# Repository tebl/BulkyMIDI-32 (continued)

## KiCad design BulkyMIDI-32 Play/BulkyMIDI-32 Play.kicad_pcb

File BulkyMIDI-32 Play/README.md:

# BulkyMIDI-32 Play
In many ways the missing module when it comes to playing around with a Roland MT-32, both the vintage kind as well as the emulated version that is the main BulkyMIDI-32 module (running mt32-pi) - simply playing back a .MID-file without a computer attached to it. Implemented with an Arduino Pro Micro at its heart, you can put your files on an SD-card and play them back - use a long press when starting playback to loop the file, another long press to stop playback. During playback the rotary encoder encoder can be used to speed up or slow down the tempo.

Given that the design includes provisions for more than the expected number of MIDI-ports, a change in firmware can allow the hardware design to be used for entirely different purposes such as MIDI-message filtering, merging inputs and similar functionality.

- [1> Building the device](#1-building-the-device)
  - [1.1> Soldering it together](#11-soldering-it-together)
  - [1.2> Without front panel](#12-without-front-panel)
  - [1.3> Including front panel](#13-including-front-panel)
  - [1.4> Finishing touches](#14-finishing-touches)
- [2> Schematic](#2-schematic)
- [3> BOM](#3-bom)

# 1> Building the device
Building a device such as this assumes you have at least minor experience soldering things together, recommended is that you at the very least have access to a soldering station with adjustable temperature. If currently available, you should probably start with 60/40 rosin core solder as the lead-free alternatives tends to be a bit harder to work with.

With requirements for basic equipment sorted, we need to talk a bit about what you want to achieve while building this project. The reason I ask is that while you can build a functional *BulkyMIDI-32 Audio Switch* by using this module by itself, but there is certainly the option of building the complete version of it - including front panels, faceplates for the top of the unit and so on. 

Now that you know what you want to build, we can get started on the most expensive step in any build process - shopping! So, head on over to the [BOM](#3-bom)-section for some information on what kind of components that you'll need. While I would have liked to give you specific part numbers for "reputable" electronic part suppliers, I can't afford to shop there so I usually make due with what I can find on sites such as ebay, AliExpress and any similar sites that sell cheap chinese components. The downside to this is that I can't link to a part directly and expect it to stay listed, so you'll need to consider the description listed as suggested search terms.

## 1.1> Soldering it together
The construction of this unit should be fairly straight-forward, just take your time in order to make sure everything goes into place - more or less straight. I usually recommend starting by having a good look at the PCBs, try to figure out where all of the listed components go and in which orientation they go in (most of the information should be clearly marked on the silkscreen).

I will usually try to install components sorted by their physical size, doing it this way means you'll have an easier time keeping everything from looking somewhat crooked. This is your board, your build and you want it perfect - don't you? If you said no, then go sit in the corner because I worked hard on creating this for myself and whoever wants to build one.

Here we've already gotten started by installing all of the resistors needed, making sure that we use the correct values for each position on the board. While doing this, it is always a good recommendation to try and keep the colour bands in the same orientation - mostly because it makes it easier to spot mistakes later on.

There are spots for a couple of 1n4148 diodes in several locations on the board, while these will not be used by the standard firmware for the *BulkyMIDI-32 Play*-module. Mostly in case I want to use the board for something else at a later point in time. The diodes are polarized, for that reason we need to pay particular attention so that the black band matches up with that of the markings on the PCB.

Sockets should be installed for the ICs, I've even added those that can be considered optional. With that in place I've also installed the monolithic disc capacitors, these are all unpolarized and for the ones without any specific markings we will install 100nF capacitors (the code *104* will be printed on them).

I added the pin headers for the *Arduino Pro Micro*, these come in variations that have slightly varying widths so one side will have two sets of pins. The Arduino itself will have female pin headers soldered to it, so this won't be an issue later - the reason for doing this way is that I might want to recycle the Arduino for a later project and this change makes it a lot easier to do so.

I'm using a fairly common *MicroSD Card Adapter* for my projects, usually you can find these in packs of three or more so they are easy to use as long as you have the board space for them (that way I don't have to think about voltage regulation when dealing with the SD-cards directly). The installation is easy, just add some thick doublesided tape to the top of the slot and insert the adapter upside down into the holes for it. It's probably not recommended to do so, but I usually just use the PCB itself to bend the right-angle pin headers until it goies into position.

Finally I added the single polarized capacitors, these need to go in the right way for them to function as expected. The stripe on the side of the capacitor denotes the negative side of it, this should be matched up with the filled in area of the footprint. I've also added a DC barrel connector (5.5mm x 2.1mm) to the board.

Add 20mm hex standoffs to each corner of the board, fixing them with nuts on the underside. Depending on your life decisions up to this point, the assembly from this point continues in one or the other direction:
- [1.2> Without front panel](#12-without-front-panel)
- [1.3> Including front panel](#13-including-front-panel)

## 1.2> Without front panel
So you resisted the temptation to build the complete version, choosing instead to cut corners where possible? Well, good for you. I'm not judging - it was just a general observation.

There's much that we need to do, mainly just install the two 5mm LEDs on the board - the longer LED pin goes into the round pad. The four switches are standard right-angle switches, the recommended way to install them is simply to solder a single pin then reheat and adjust its alignment before soldering in the rest of the pins.

- [1.4> Finishing touches](#14-finishing-touches)

## 1.3> Including front panel

The [Play Panel](https://github.com/tebl/BulkyMIDI-32/tree/main/BulkyMIDI-32%20Play%20Panel) have its own set of documentation going into the various steps required to put it together correctly, a finished unit have already been installed on the device as shown already. The clue to get it right is ensuring that one of the *flat* sides of the 20mm standoffs point towards the inside of the PCB. With the alignment correct you should be able to insert the panel into the board without too much force, if you have one I recommend that you try installing your selected faceplate on top of the device using screws.

At this point we've not actually soldered the various boards together, mostly to ensure that everything comes together correctly before we actually do so. Push the panel firmly so that it sits towards the back of the cutouts, before finally soldering the pins into place - afterwards we just make sure to trim the excess parts of the pin headers from the underside of the device to prevent any accidental shorting.

- [1.4> Finishing touches](#14-finishing-touches)

## 1.4> Finishing touches

If you've made it this far, you're almost ready to simply start using it. What's missing in order to test it is the single IC that needs to be inserted into the socket, so just get that out of the way before you forget to do so. The device is powered using a 5v DC barrel jack (center positive). These should be easy to obtain from your favourite electronics vendor, just make sure that it's from a somewhat respected brand.

The only step that's remaining to do when it comes to the hardware is just to screw the faceplates back on the top of the device, once that's in place we can also add the front panel as well.

The [firmware](https://github.com/tebl/BulkyMIDI-32/tree/main/software/arduino/Play) that was developed for the device have been included in the software-portion of this repository. The code itself was written using PlatformIO environment though it should be compilable using the standard *Arduino IDE*, if you should prefer to do so. 

# 2> Schematic
The supplied KiCad files should be sufficient as both a schematic and as a  starting point for ordering PCBs (basically you could just zip the contents of the export folder and upload that on a fabrication site), the schematic is also available in [PDF-format](https://github.com/tebl/BulkyMIDI-32/tree/main/documentation/schematic) and this is what you'll need to print and work your way through this things don't work as expected after assembly.

# 3> BOM
Most parts should be easy to get a hold of from your favourite local electronic component shop, but given that I don't have access to such shops where I live so everything was based on whatever I could get cheapest from eBay/AliExpress (free shipping, but plan on waiting 3-4 weeks for delivery). Components in parenthesis can be considered optional for features beyond the more basic functionality, but where's the fun in that? You deserve the complete package.

| Reference             | Item                                                              | Count | Order  |
| --------------------- | ----------------------------------------------------------------- | ----- | ------ |
| PCB                   | Fabricate using Gerber files                                      |     1 | PCBWay
| [Panel PCB](https://github.com/tebl/BulkyMIDI-32/tree/main/BulkyMIDI-32%20Play%20Panel) | Fabricate using Gerber files                                      |    (1)| PCBWay
| A1                    | Arduino Pro Micro                                                 |     1 |
|                       |  - Breakable straight pin headers                                 |     1 |
|                       |  - 12-pin female pin header                                       |     2 |
| A2                    | MicroSD Card Adapter module                                       |     1 |
| C1                    | 100nF ceramic capacitor (5mm)                                     |     1 |
| C2,C7                 | 100nF ceramic capacitor (5mm)                                     |    (2)|
| C6                    | 470uF electrolytic capacitor (8mm x 3.5mm)                        |     1 |
| D1,D2 *               | 5mm LED                                                           |    (2)|
| D3,D4                 | 1N4148N small signal diode (DO-35)                                |    (2)|
| IC1 *                 | 0.91 inch oled display                                            |    (1)|
| J1                    | 2.1mm x 5.5mm barrel plug                                         |     1 |
| JP1                   | Breakable straight pin header and jumper cap                      |     1 |
| R1-R3,R6,R8-R10,R18   | 220 ohm resistor                                                  |     8 |
| R4,R5                 | 330 ohm resistor                                                  |     2 |
| R7,R19                | 2kk (2200) ohm resistor                                           |     2 |
| SW1-SW6 *             | 6x6x5mm right-angle momentary button                              |    (4)|
| U1                    | 74HCT14 (DIP-14)                                                  |     1 |
| Mounting ****         | Nylon M3 hex standoffs 20mm (M-F)                                 |     4 |
| Mounting ****         | Nylon M3x6mm nylon screws                                         |     4 |
| Mounting ****         | Nylon M3x6mm nylon nuts                                           |     4 |

*) You can choose to install a front panel, in which case you would skip the installation of the 3mm LED as well as the switches. The resistors will be used by the front panel.

****) These are available in the form of kits usually advertised *M3 nylon standoff kit* which should contain most of what you'd need. I do however recommend that you pick up extra M-F standoffs of lengths 8mm and 20mm, as quite a lot of them will be used when building more than one module.

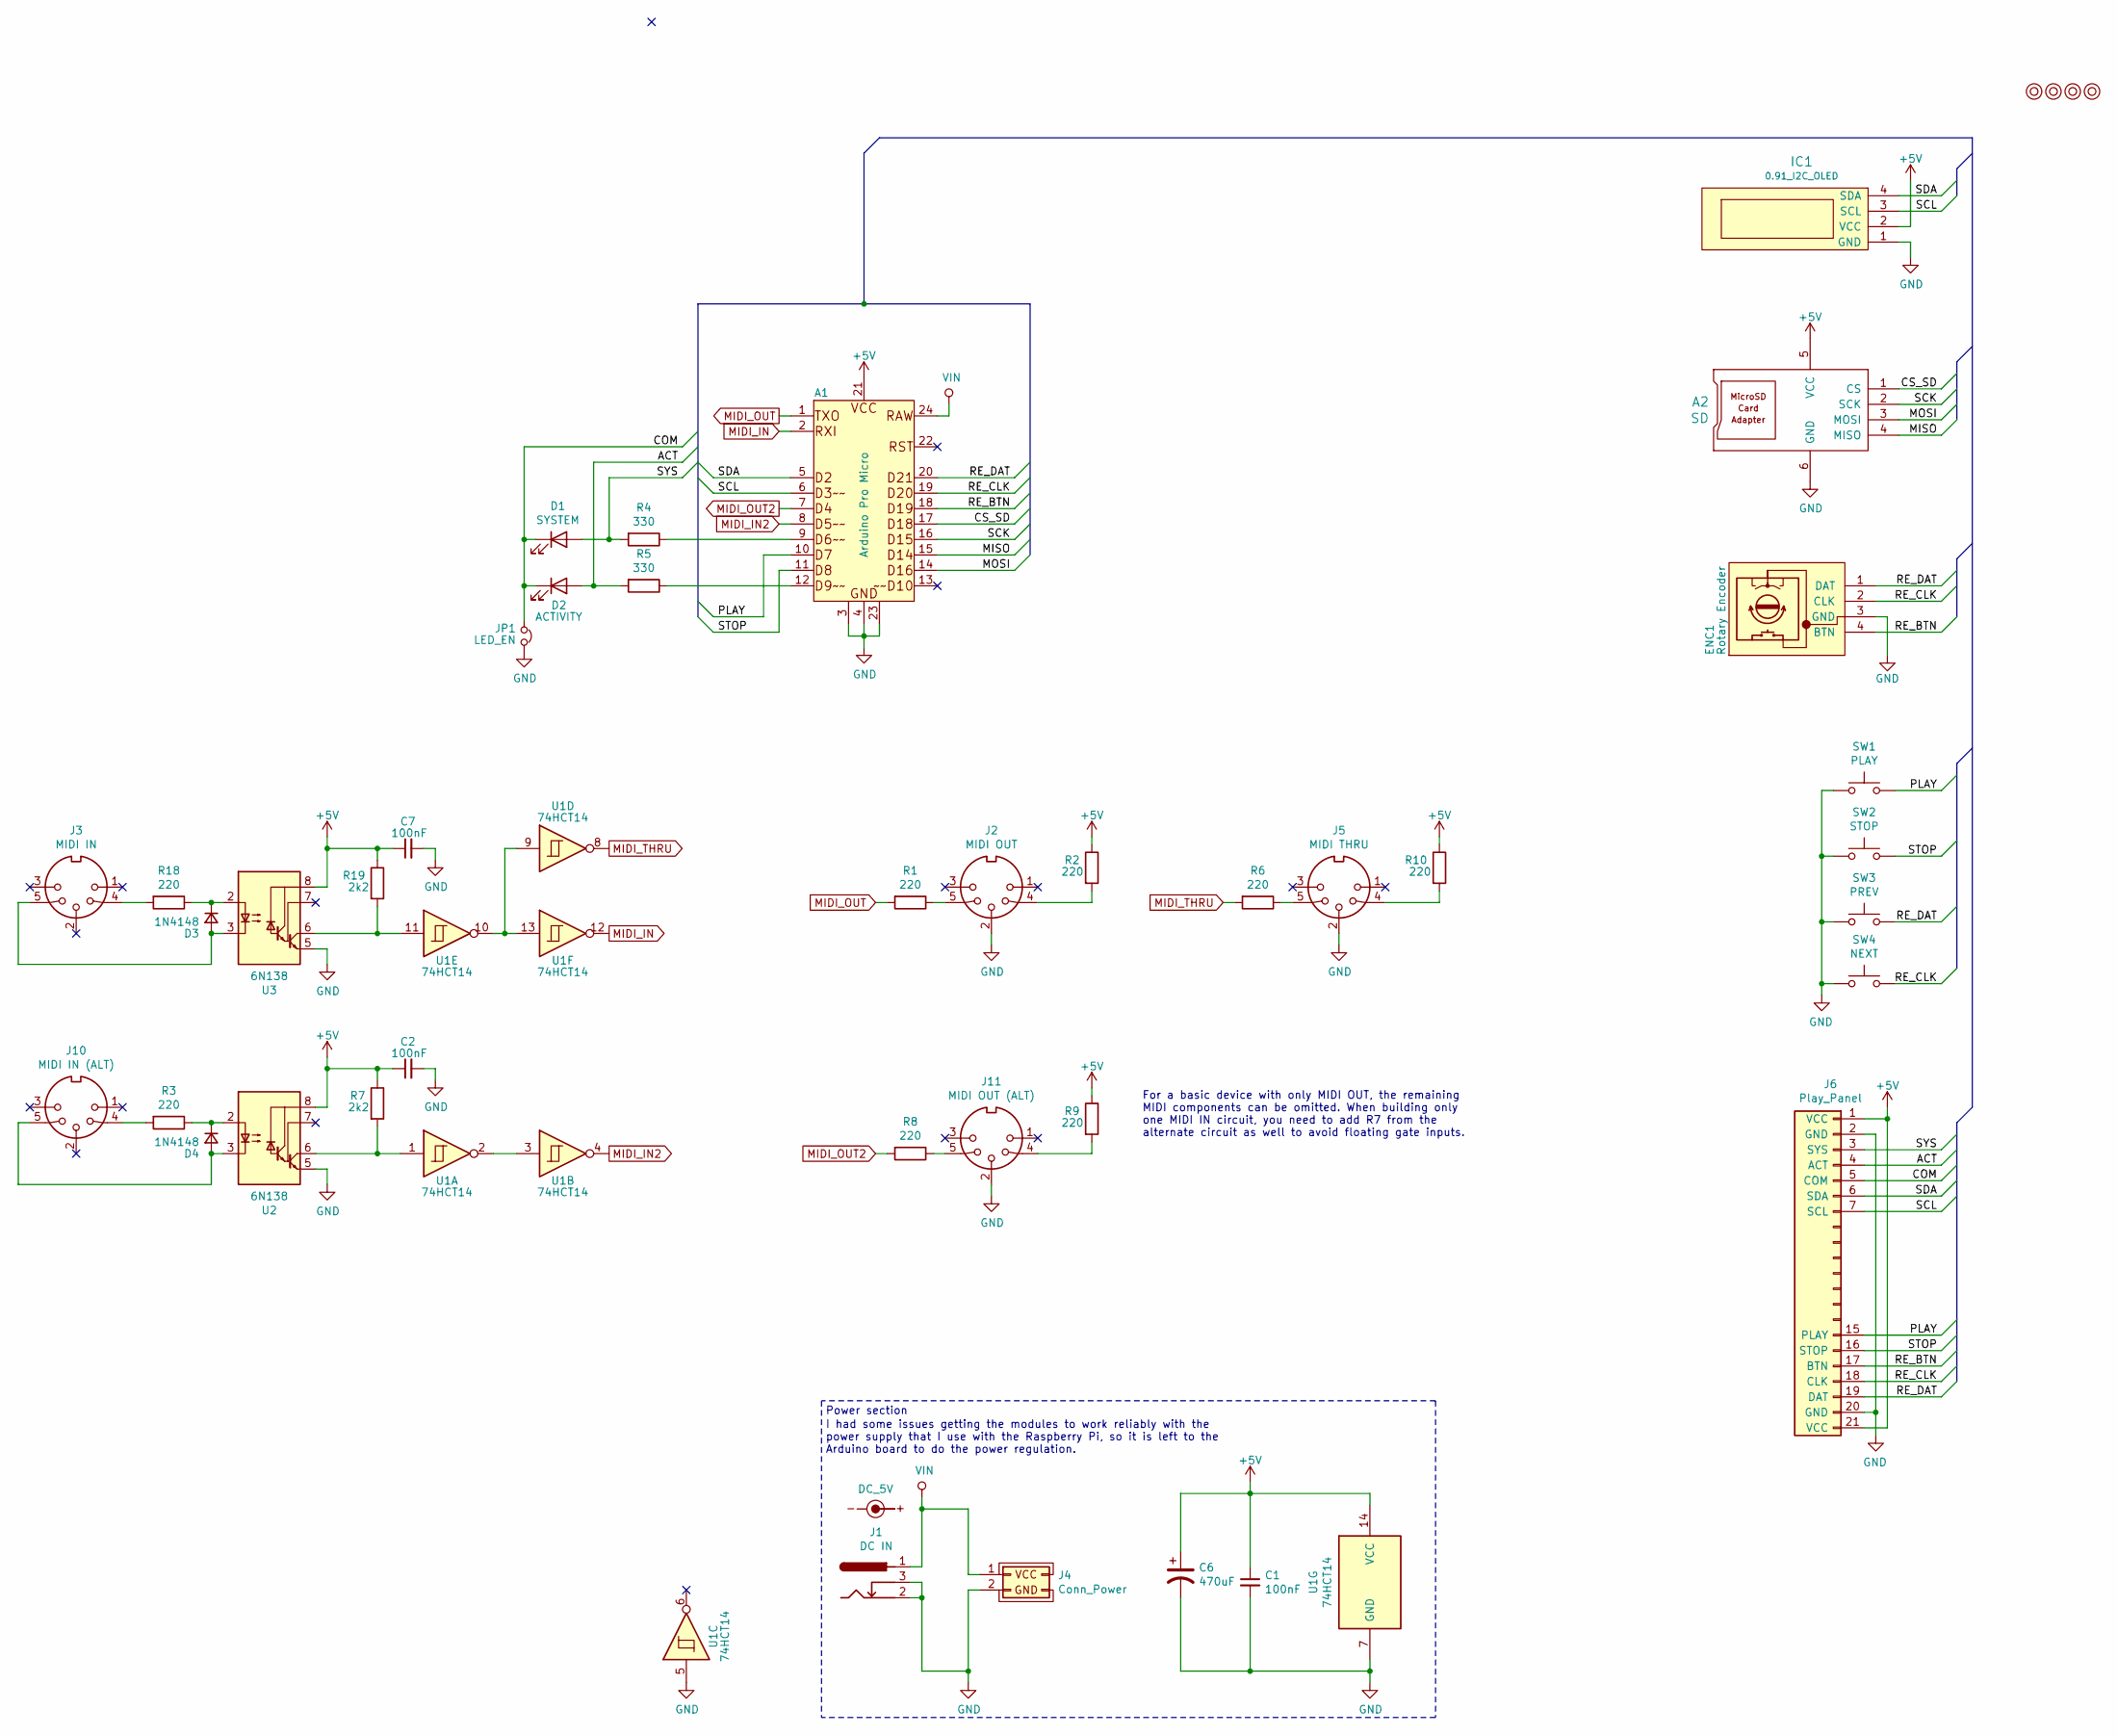
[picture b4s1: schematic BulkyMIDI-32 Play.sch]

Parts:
A1: Arduino Pro Micro; Arduino_Pro_Micro
A2: SD; MicroSD_Card_Adapter
C1, C2, C7: 100nF; C_Disc_D4.7mm_W2.5mm_P5.00mm
C6: 470uF; CP_Radial_D8.0mm_P3.50mm
D1: SYSTEM; LED_D5.0mm
D2: ACTIVITY; LED_D5.0mm
D3, D4: 1N4148; D_DO-35_SOD27_P7.62mm_Horizontal
ENC1: Rotary Encoder; PinHeader_1x04_P2.54mm_Vertical
IC1: 0.91_I2C_OLED; PinHeader_1x04_P2.54mm_Vertical
J1: DC IN; BARREL_JACK
J2: MIDI OUT; DIN5_MIDI
J3: MIDI IN; DIN5_MIDI
J4: Conn_Power
J5: MIDI THRU; DIN5_MIDI
J6: Play_Panel
J10: MIDI IN (ALT); DIN5_MIDI
J11: MIDI OUT (ALT); DIN5_MIDI
JP1: LED_EN; PinHeader_1x02_P2.54mm_Vertical
M1, M2, M3, M4: Mounting; M3
R1, R2, R3, R6, R8, R9, R10, R18: 220; R_Axial_DIN0207_L6.3mm_D2.5mm_P10.16mm_Horizontal
R4, R5: 330; R_Axial_DIN0207_L6.3mm_D2.5mm_P10.16mm_Horizontal
R7, R19: 2k2; R_Axial_DIN0207_L6.3mm_D2.5mm_P10.16mm_Horizontal
SW1: PLAY; SW_Tactile_SPST_Angled_PTS645Vx39-2LFS
SW2: STOP; SW_Tactile_SPST_Angled_PTS645Vx39-2LFS
SW3: PREV; SW_Tactile_SPST_Angled_PTS645Vx39-2LFS
SW4: NEXT; SW_Tactile_SPST_Angled_PTS645Vx39-2LFS
SYM1: DC_5V; PWR_Specification
U1: 74HCT14; DIP-14_W7.62mm_Socket_LongPads
U2, U3: 6N138; DIP-8_W7.62mm_Socket_LongPads

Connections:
+5V: A1.21 (VCC), A2.5 (VCC), C1.1, C2.1, C6.1, C7.1, IC1.2 (VCC), J6.1 (VCC), J6.21 (VCC), R2.1, R7.1, R9.1, R10.1, R19.1, U1.14 (VCC), U2.8 (VCC), U3.8 (VCC)
/ACT: D2.2 (A), J6.4 (ACT), R5.2
/COM: D1.1 (K), D2.1 (K), J6.5 (COM), JP1.2
/CS_SD: A1.17 (D18), A2.1 (CS)
/MISO: A1.15 (D14), A2.4 (MISO)
/MOSI: A1.14 (D16), A2.3 (MOSI)
/PLAY: A1.10 (D7), J6.15 (PLAY), SW1.1
/RE_BTN: A1.18 (D19), ENC1.4 (BTN), J6.17 (BTN)
/RE_CLK: A1.19 (D20), ENC1.2 (CLK), J6.18 (CLK), SW4.1
/RE_DAT: A1.20 (D21), ENC1.1 (DAT), J6.19 (DAT), SW3.1
/SCK: A1.16 (D15), A2.2 (SCK)
/SCL: A1.6 (D3), IC1.3 (SCL), J6.7 (SCL)
/SDA: A1.5 (D2), IC1.4 (SDA), J6.6 (SDA)
/STOP: A1.11 (D8), J6.16 (STOP), SW2.1
/SYS: D1.2 (A), J6.3 (SYS), R4.2
GND: A1.3 (GND), A1.4 (GND), A1.23 (GND), A2.6 (GND), C1.2, C2.2, C6.2, C7.2, ENC1.3 (GND), IC1.1 (GND), J1.2, J1.3, J2.2, J4.2 (GND), J5.2, J6.2 (GND), J6.20 (GND), J11.2, JP1.1, SW1.2, SW2.2, SW3.2, SW4.2, U1.5, U1.7 (GND), U2.5 (GND), U3.5 (GND)
MIDI_IN: A1.2 (RXI), U1.12
MIDI_IN2: A1.8 (D5), U1.4
MIDI_OUT: A1.1 (TXO), R1.2
MIDI_OUT2: A1.7 (D4), R8.2
MIDI_THRU: R6.2, U1.8
unnamed: A1.9 (D6), R4.1
unnamed: A1.12 (D9), R5.1
unnamed: D3.1 (K), R18.1, U3.2 (C1)
unnamed: D3.2 (A), J3.5, U3.3 (C2)
unnamed: D4.1 (K), R3.1, U2.2 (C1)
unnamed: D4.2 (A), J10.5, U2.3 (C2)
unnamed: J2.4, R2.2
unnamed: J2.5, R1.1
unnamed: J3.4, R18.2
unnamed: J5.4, R10.2
unnamed: J5.5, R6.1
unnamed: J10.4, R3.2
unnamed: J11.4, R9.2
unnamed: J11.5, R8.1
unnamed: R7.2, U1.1, U2.6 (VO2)
unnamed: R19.2, U1.11, U3.6 (VO2)
unnamed: U1.2, U1.3
unnamed: U1.9, U1.10, U1.13
VIN: A1.24 (RAW), J1.1, J4.1 (VCC)

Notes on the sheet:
Power section
For a basic device with only MIDI OUT, the remaining MIDI components can be omitted. When building only one MIDI IN circuit, you need to add R7 from the alternate circuit as well to avoid floating gate inputs.
I had some issues getting the modules to work reliably with the power supply that I use with the Raspberry Pi, so it is left to the Arduino board to do the power regulation.

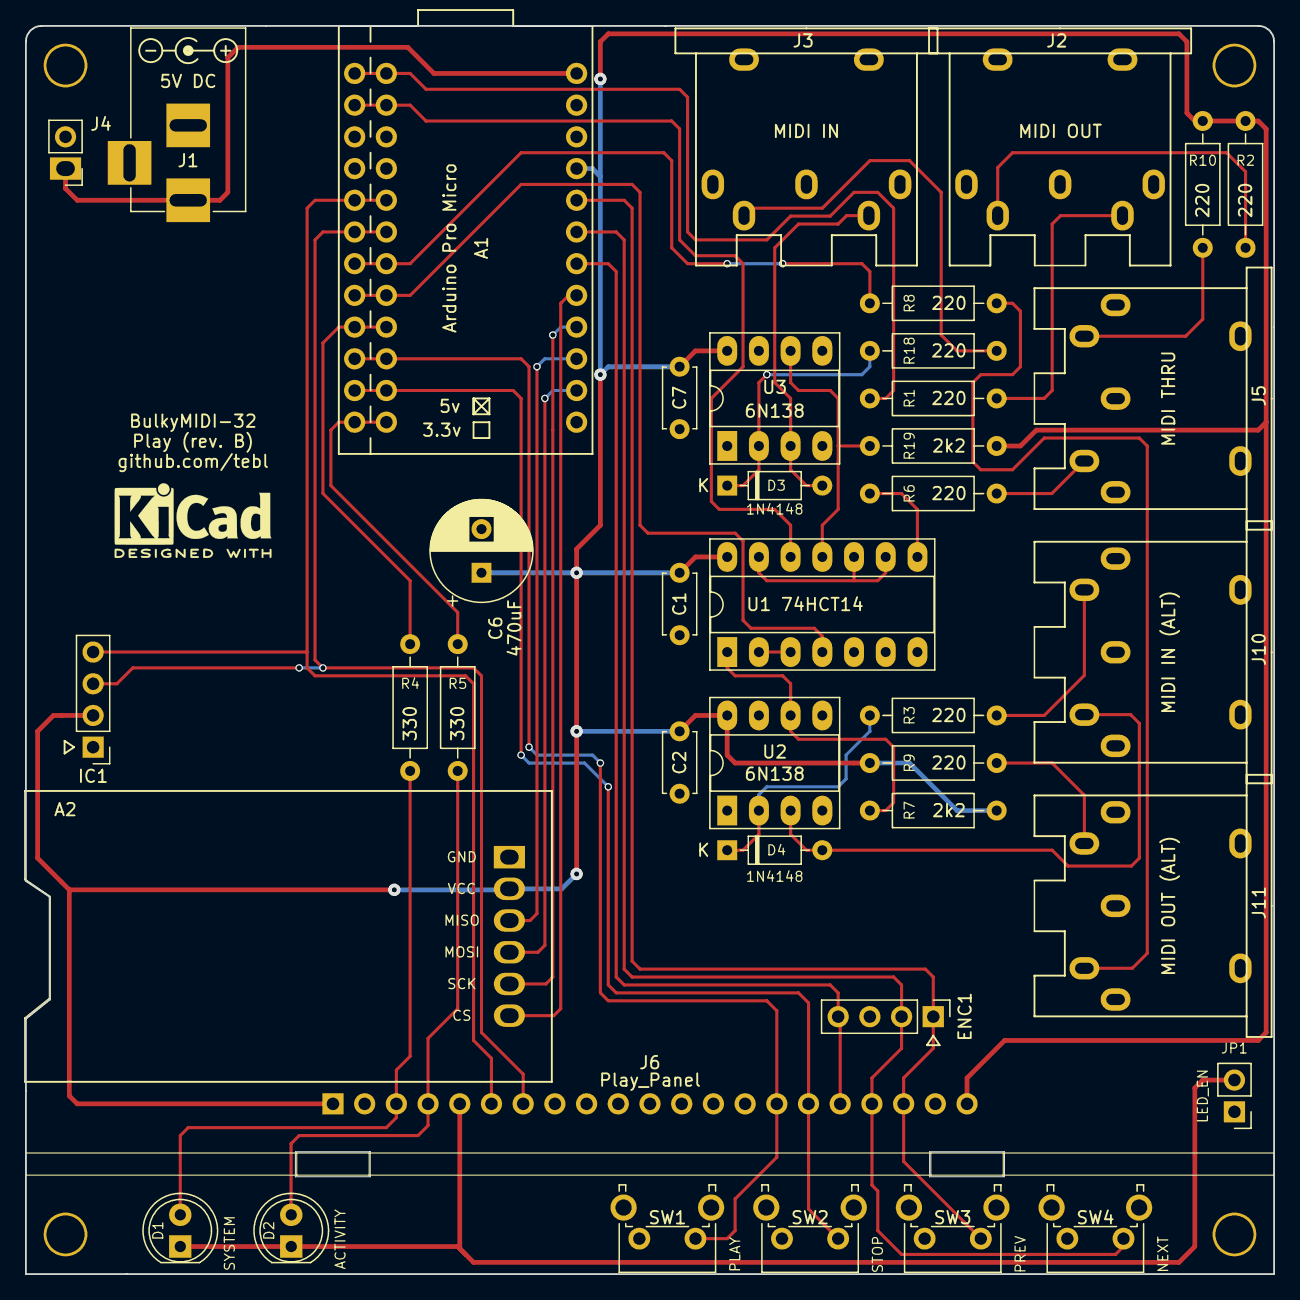
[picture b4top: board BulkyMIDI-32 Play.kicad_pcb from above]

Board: 2 copper layers, 100.0 x 100.0 mm, 45 parts (0 on the bottom side), 40 nets.

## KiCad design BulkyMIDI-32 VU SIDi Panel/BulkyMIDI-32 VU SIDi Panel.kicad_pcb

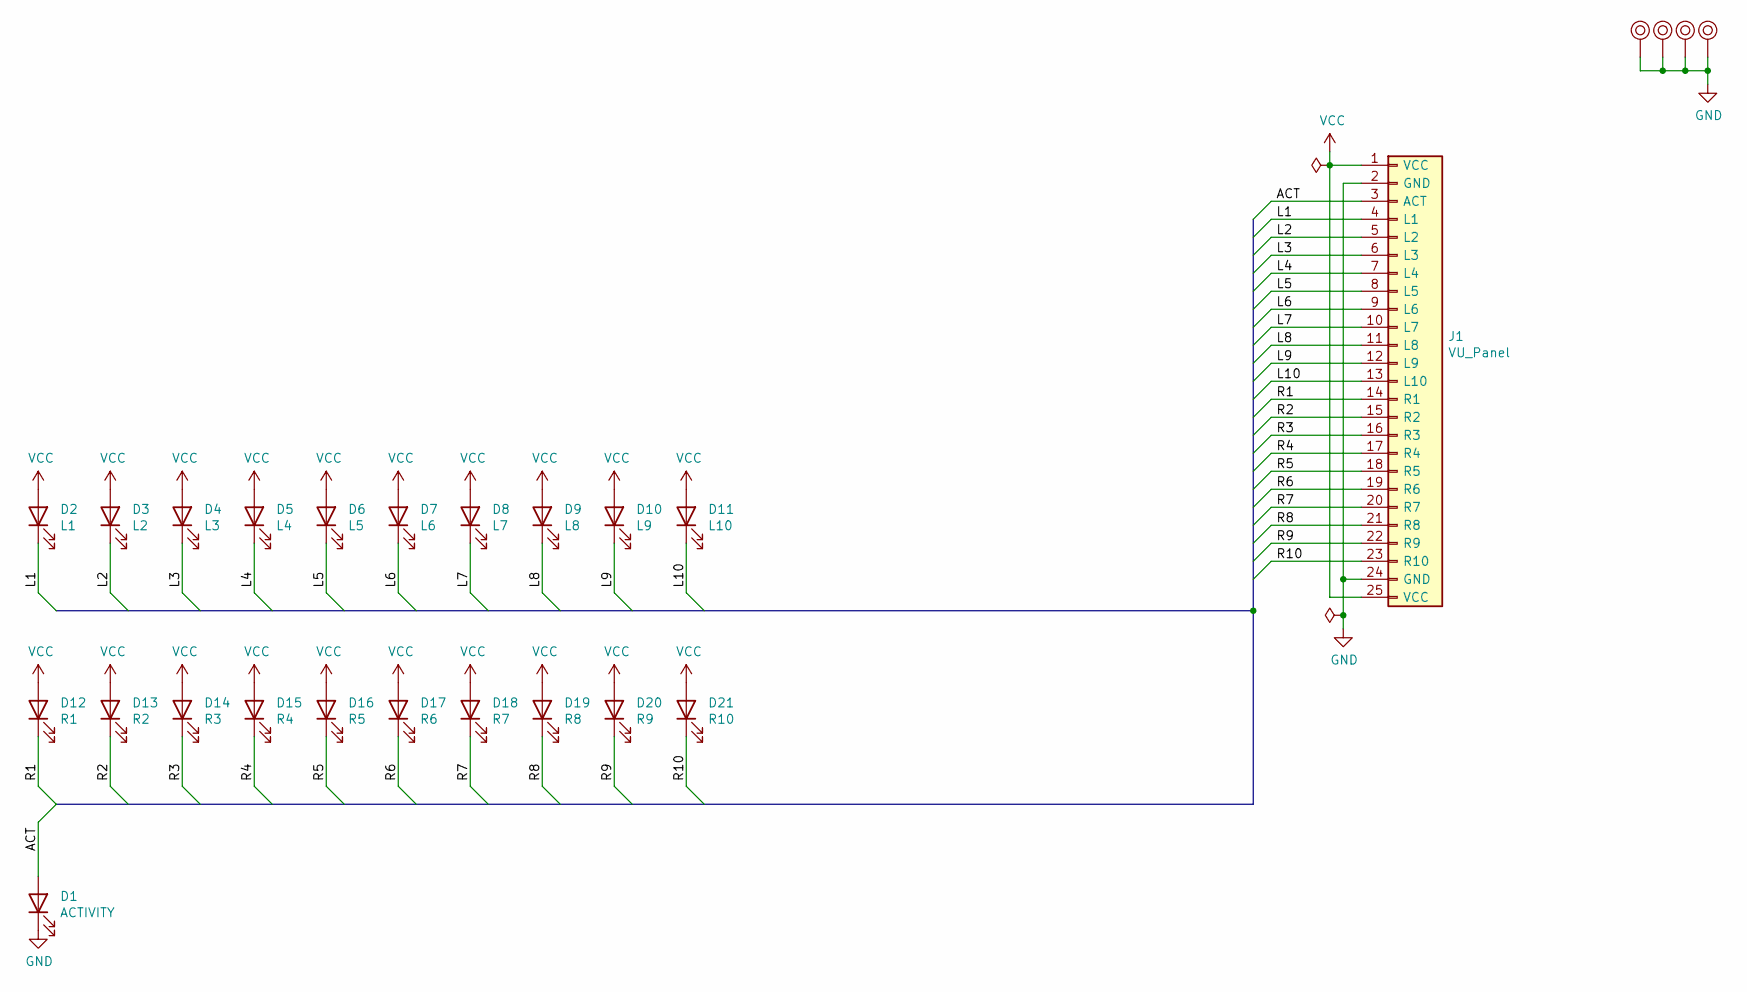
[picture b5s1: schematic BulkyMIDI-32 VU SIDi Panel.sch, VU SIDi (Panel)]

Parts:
D1: ACTIVITY; LED_D5.0mm
D2: L1; LED_D5.0mm
D3: L2; LED_D5.0mm
D4: L3; LED_D5.0mm
D5: L4; LED_D5.0mm
D6: L5; LED_D5.0mm
D7: L6; LED_D5.0mm
D8: L7; LED_D5.0mm
D9: L8; LED_D5.0mm
D10: L9; LED_D5.0mm
D11: L10; LED_D5.0mm
D12: R1; LED_D5.0mm
D13: R2; LED_D5.0mm
D14: R3; LED_D5.0mm
D15: R4; LED_D5.0mm
D16: R5; LED_D5.0mm
D17: R6; LED_D5.0mm
D18: R7; LED_D5.0mm
D19: R8; LED_D5.0mm
D20: R9; LED_D5.0mm
D21: R10; LED_D5.0mm
J1: VU_Panel; PinHeader_1x25_P2.54mm_Horizontal
M1, M2, M3, M4: Mounting_Pin; M3_pin

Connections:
/ACT: D1.2 (A), J1.3 (ACT)
/L1: D2.1 (K), J1.4 (L1)
/L2: D3.1 (K), J1.5 (L2)
/L3: D4.1 (K), J1.6 (L3)
/L4: D5.1 (K), J1.7 (L4)
/L5: D6.1 (K), J1.8 (L5)
/L6: D7.1 (K), J1.9 (L6)
/L7: D8.1 (K), J1.10 (L7)
/L8: D9.1 (K), J1.11 (L8)
/L9: D10.1 (K), J1.12 (L9)
/L10: D11.1 (K), J1.13 (L10)
/R1: D12.1 (K), J1.14 (R1)
/R2: D13.1 (K), J1.15 (R2)
/R3: D14.1 (K), J1.16 (R3)
/R4: D15.1 (K), J1.17 (R4)
/R5: D16.1 (K), J1.18 (R5)
/R6: D17.1 (K), J1.19 (R6)
/R7: D18.1 (K), J1.20 (R7)
/R8: D19.1 (K), J1.21 (R8)
/R9: D20.1 (K), J1.22 (R9)
/R10: D21.1 (K), J1.23 (R10)
GND: D1.1 (K), J1.2 (GND), J1.24 (GND), M1.1, M2.1, M3.1, M4.1
VCC: D2.2 (A), D3.2 (A), D4.2 (A), D5.2 (A), D6.2 (A), D7.2 (A), D8.2 (A), D9.2 (A), D10.2 (A), D11.2 (A), D12.2 (A), D13.2 (A), D14.2 (A), D15.2 (A), D16.2 (A), D17.2 (A), D18.2 (A), D19.2 (A), D20.2 (A), D21.2 (A), J1.1 (VCC), J1.25 (VCC)

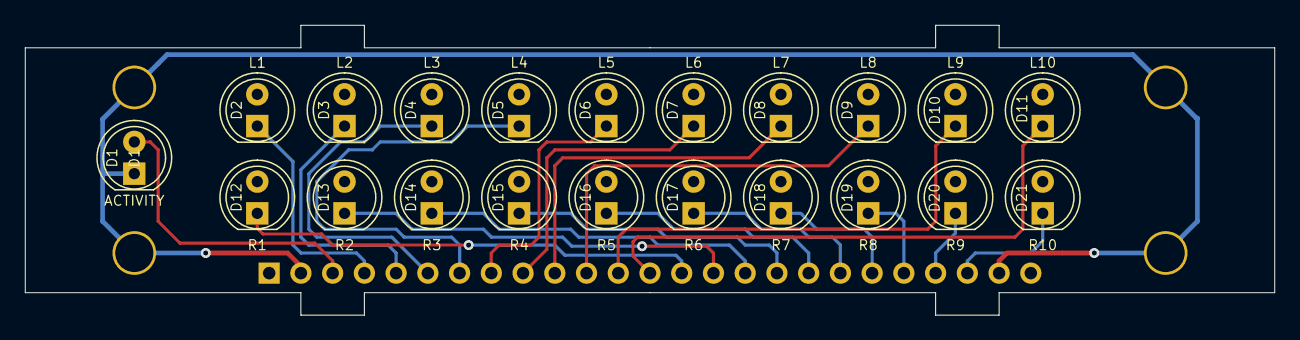
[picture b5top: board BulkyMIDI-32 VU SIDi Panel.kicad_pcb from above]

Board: 2 copper layers, 100.0 x 23.2 mm, 26 parts (1 on the bottom side), 23 nets.

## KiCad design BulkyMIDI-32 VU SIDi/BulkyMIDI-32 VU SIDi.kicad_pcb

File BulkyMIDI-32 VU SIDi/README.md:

# BulkyMIDI-32 VU SIDi
**UNTESTED**
A combination of LM3915-based VU-meters and a version of the [SIDI](https://github.com/doctea/SIDI)-project.

The VU-meter circuit was built from the *Simplified VU-meter* on the following [article](https://www.homemade-circuits.com/how-to-make-simple-vu-meter-circuit-at/).

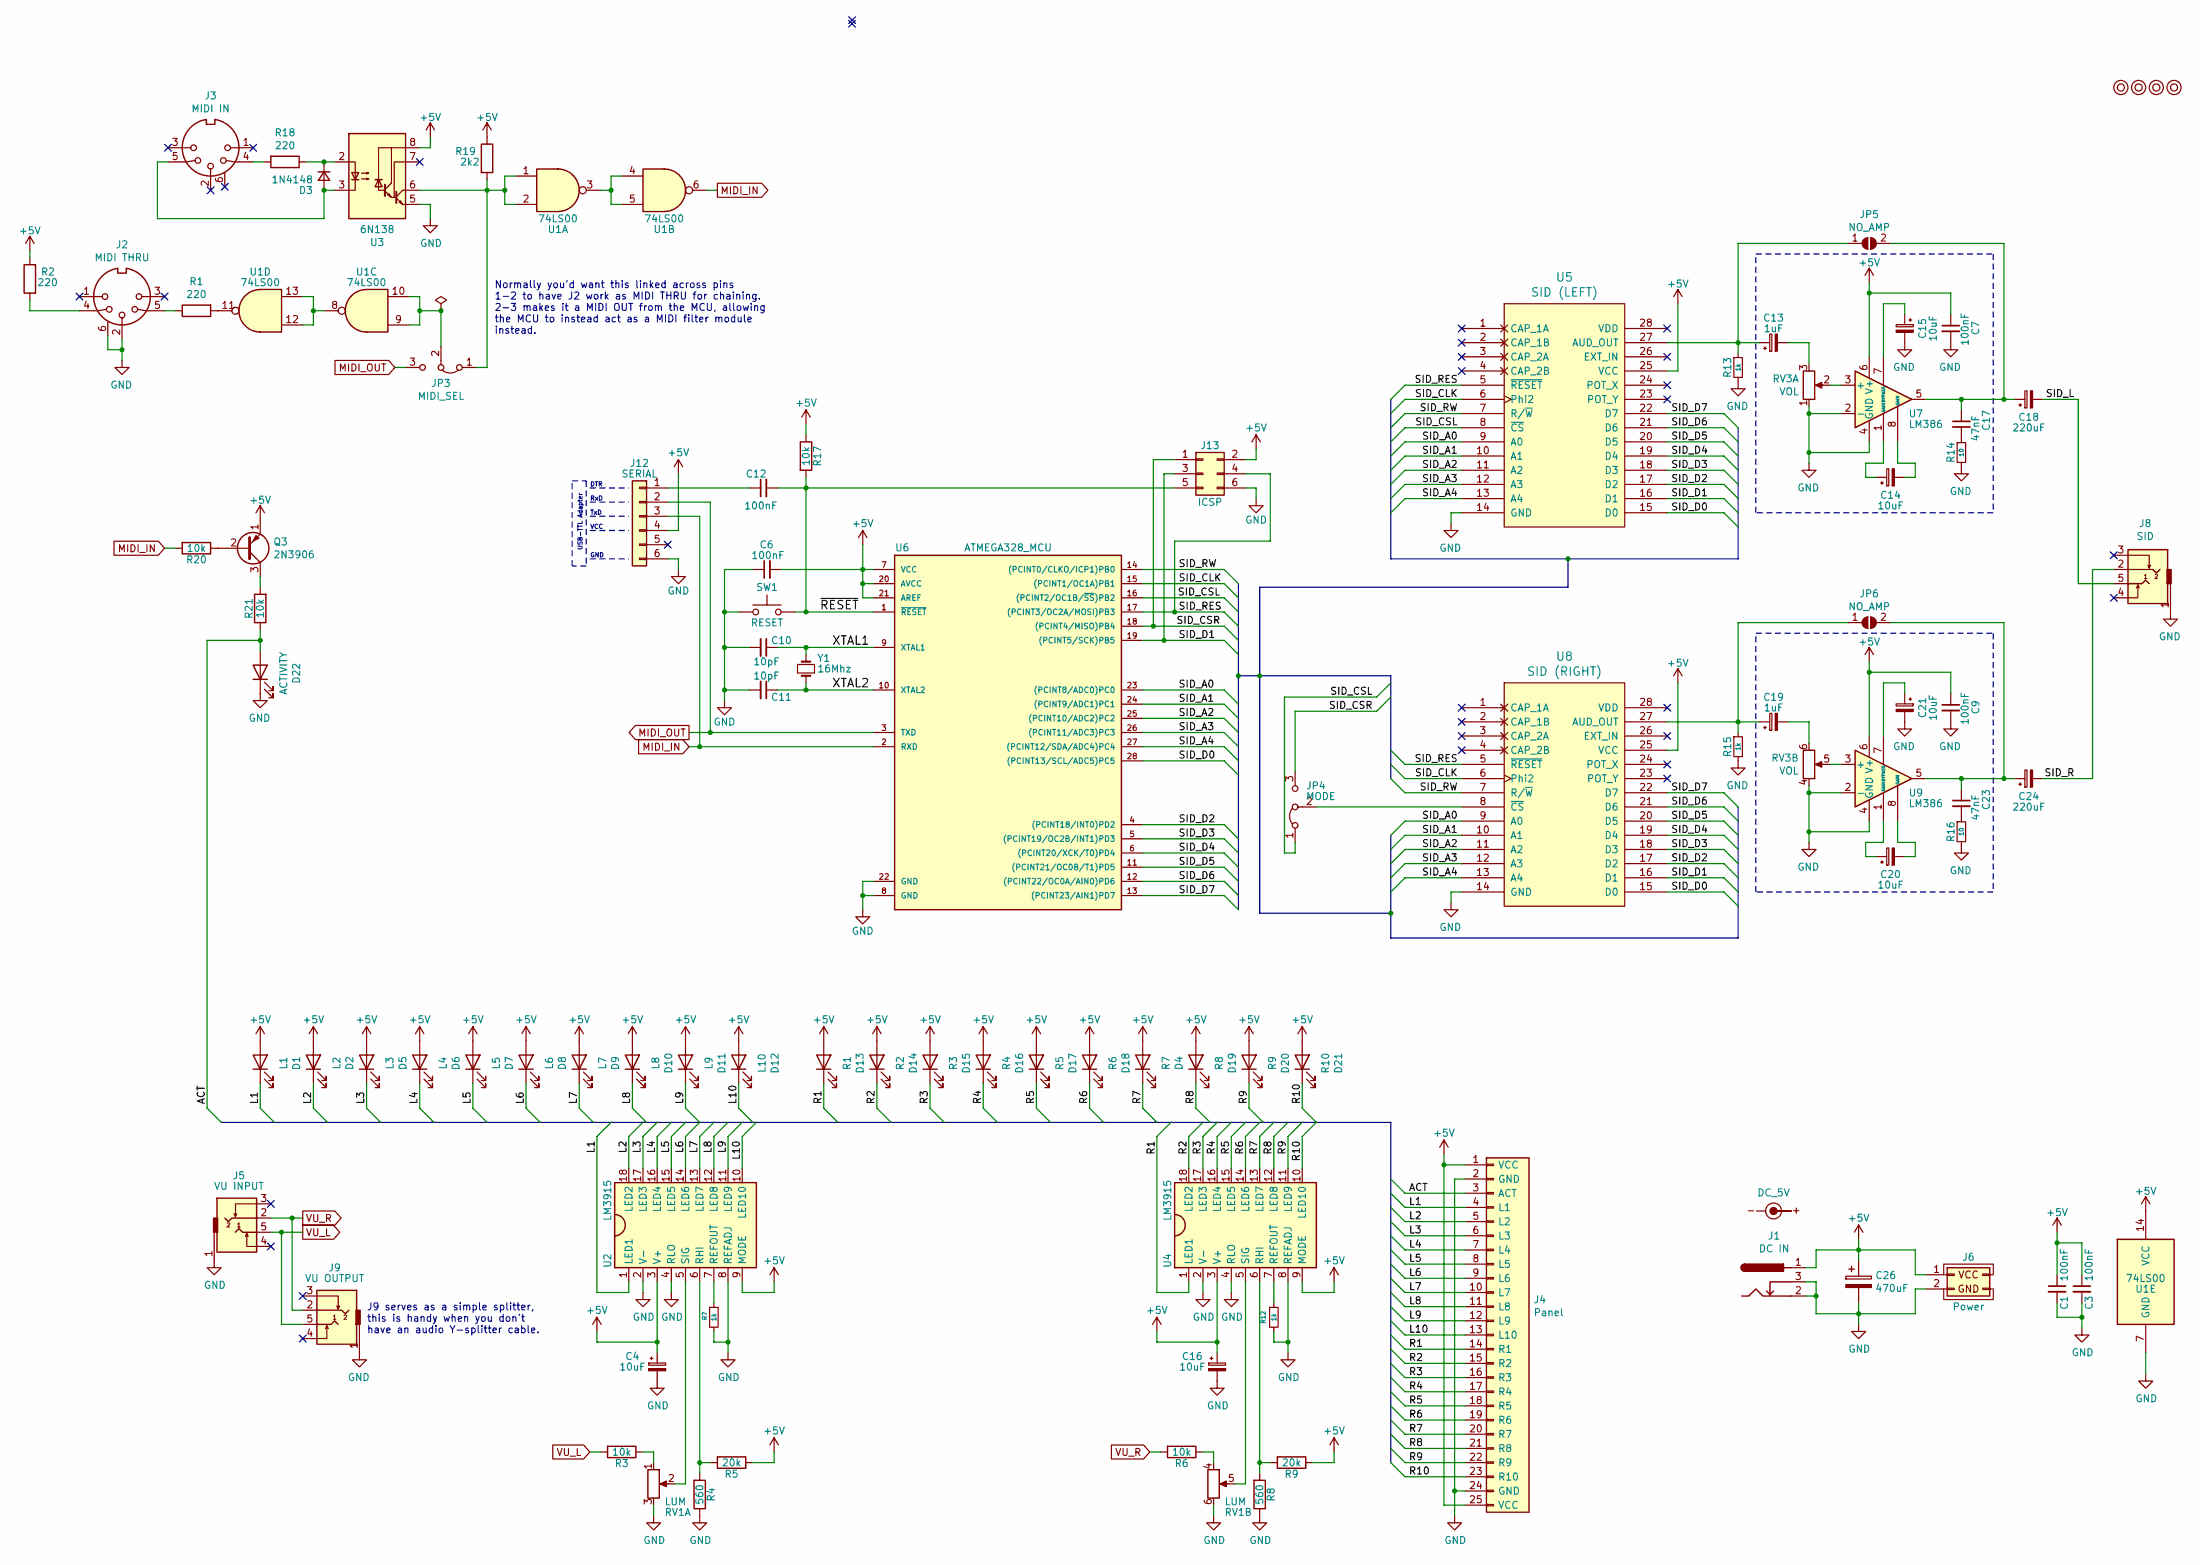
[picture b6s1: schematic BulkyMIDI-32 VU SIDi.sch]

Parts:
C1, C3, C6, C7, C9, C12: 100nF; C_Disc_D4.7mm_W2.5mm_P5.00mm
C4, C14, C15, C16, C20, C21: 10uF; CP_Radial_D4.0mm_P2.00mm
C10, C11: 10pF; C_Disc_D4.7mm_W2.5mm_P5.00mm
C13, C19: 1uF; CP_Radial_D4.0mm_P2.00mm
C17, C23: 47nF; C_Disc_D4.7mm_W2.5mm_P5.00mm
C18, C24: 220uF; CP_Radial_D6.3mm_P2.50mm
C26: 470uF; CP_Radial_D8.0mm_P3.50mm
D1: L1; LED_D3.0mm
D2: L2; LED_D3.0mm
D3: 1N4148; D_DO-35_SOD27_P7.62mm_Horizontal
D4: R7; LED_D3.0mm
D5: L3; LED_D3.0mm
D6: L4; LED_D3.0mm
D7: L5; LED_D3.0mm
D8: L6; LED_D3.0mm
D9: L7; LED_D3.0mm
D10: L8; LED_D3.0mm
D11: L9; LED_D3.0mm
D12: L10; LED_D3.0mm
D13: R1; LED_D3.0mm
D14: R2; LED_D3.0mm
D15: R3; LED_D3.0mm
D16: R4; LED_D3.0mm
D17: R5; LED_D3.0mm
D18: R6; LED_D3.0mm
D19: R8; LED_D3.0mm
D20: R9; LED_D3.0mm
D21: R10; LED_D3.0mm
D22: ACTIVITY; LED_D3.0mm
J1: DC IN; BARREL_JACK
J2: MIDI THRU; DIN5_MIDI_OUT
J3: MIDI IN; DIN5_MIDI_IN
J4: Panel; VU_SIDI_Panel
J5: VU INPUT; PJ-317_IN
J6: Power; Conn_Power
J8: SID; PJ-317_OUT
J9: VU OUTPUT; PJ-317_OUT
J12: SERIAL; PinHeader_1x06_P2.54mm_Vertical
J13: ICSP; PinHeader_2x03_P2.54mm_Vertical
JP3: MIDI_SEL; PinHeader_1x03_P2.54mm_Vertical
JP4: MODE; PinHeader_1x03_P2.54mm_Vertical
JP5, JP6: NO_AMP; SolderJumper-2_P1.3mm_Open_Pad1.0x1.5mm
M1, M2, M3, M4: Mounting; M3
Q3: 2N3906; TO-92_Inline_Wide
R1, R2, R18: 220; R_Axial_DIN0207_L6.3mm_D2.5mm_P10.16mm_Horizontal
R3, R6, R17, R20, R21: 10k; R_Axial_DIN0207_L6.3mm_D2.5mm_P10.16mm_Horizontal
R4, R8: 560; R_Axial_DIN0207_L6.3mm_D2.5mm_P10.16mm_Horizontal
R5, R9: 20k; R_Axial_DIN0207_L6.3mm_D2.5mm_P10.16mm_Horizontal
R7, R12, R13, R15: 1k; R_Axial_DIN0207_L6.3mm_D2.5mm_P10.16mm_Horizontal
R14, R16: 10; R_Axial_DIN0207_L6.3mm_D2.5mm_P10.16mm_Horizontal
R19: 2k2; R_Axial_DIN0207_L6.3mm_D2.5mm_P10.16mm_Horizontal
RV1: LUM; RK097G
RV3: VOL; RK097G
SW1: RESET; SW_PUSH_6mm
SYM1: DC_5V; PWR_Specification
U1: 74LS00; DIP-14_W7.62mm_Socket_LongPads
U2, U4: LM3915; DIP-18_W7.62mm_Socket_LongPads
U3: 6N138; DIP-8_W7.62mm_Socket_LongPads
U5: SID (LEFT); DIP-28_W15.24mm_Socket_LongPads
U6: ATMEGA328_MCU; DIP-28_W7.62mm_Socket_LongPads
U7, U9: LM386; DIP-8_W7.62mm_Socket_LongPads
U8: SID (RIGHT); DIP-28_W15.24mm_Socket_LongPads
Y1: 16Mhz; Crystal_HC49-4H_Vertical

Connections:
+5V: C1.1, C3.1, C4.1, C6.2, C7.1, C9.1, C16.1, C26.1, D1.2 (A), D2.2 (A), D4.2 (A), D5.2 (A), D6.2 (A), D7.2 (A), D8.2 (A), D9.2 (A), D10.2 (A), D11.2 (A), D12.2 (A), D13.2 (A), D14.2 (A), D15.2 (A), D16.2 (A), D17.2 (A), D18.2 (A), D19.2 (A), D20.2 (A), D21.2 (A), J1.1, J4.1 (VCC), J4.25 (VCC), J6.1 (VCC), J12.4, J13.2, Q3.1 (E), R2.1, R5.1, R9.1, R17.1, R19.1, U1.14 (VCC), U2.3 (V+), U2.9 (MODE), U3.8 (VCC), U4.3 (V+), U4.9 (MODE), U5.25 (VCC), U6.7 (VCC), U6.20 (AVCC), U6.21 (AREF), U7.6 (V+), U8.25 (VCC), U9.6 (V+)
/ACT: D22.2 (A), J4.3 (ACT), R21.1
/L1: D1.1 (K), J4.4 (L1), U2.1 (LED1)
/L2: D2.1 (K), J4.5 (L2), U2.18 (LED2)
/L3: D5.1 (K), J4.6 (L3), U2.17 (LED3)
/L4: D6.1 (K), J4.7 (L4), U2.16 (LED4)
/L5: D7.1 (K), J4.8 (L5), U2.15 (LED5)
/L6: D8.1 (K), J4.9 (L6), U2.14 (LED6)
/L7: D9.1 (K), J4.10 (L7), U2.13 (LED7)
/L8: D10.1 (K), J4.11 (L8), U2.12 (LED8)
/L9: D11.1 (K), J4.12 (L9), U2.11 (LED9)
/L10: D12.1 (K), J4.13 (L10), U2.10 (LED10)
/R1: D13.1 (K), J4.14 (R1), U4.1 (LED1)
/R2: D14.1 (K), J4.15 (R2), U4.18 (LED2)
/R3: D15.1 (K), J4.16 (R3), U4.17 (LED3)
/R4: D16.1 (K), J4.17 (R4), U4.16 (LED4)
/R5: D17.1 (K), J4.18 (R5), U4.15 (LED5)
/R6: D18.1 (K), J4.19 (R6), U4.14 (LED6)
/R7: D4.1 (K), J4.20 (R7), U4.13 (LED7)
/R8: D19.1 (K), J4.21 (R8), U4.12 (LED8)
/R9: D20.1 (K), J4.22 (R9), U4.11 (LED9)
/R10: D21.1 (K), J4.23 (R10), U4.10 (LED10)
/SID_A0: U5.9 (A0), U6.23 ((PCINT8/ADC0)PC0), U8.9 (A0)
/SID_A1: U5.10 (A1), U6.24 ((PCINT9/ADC1)PC1), U8.10 (A1)
/SID_A2: U5.11 (A2), U6.25 ((PCINT10/ADC2)PC2), U8.11 (A2)
/SID_A3: U5.12 (A3), U6.26 ((PCINT11/ADC3)PC3), U8.12 (A3)
/SID_A4: U5.13 (A4), U6.27 ((PCINT12/SDA/ADC4)PC4), U8.13 (A4)
/SID_CLK: U5.6 (Phi2), U6.15 ((PCINT1/OC1A)PB1), U8.6 (Phi2)
/SID_CSL: JP4.1 (A), U5.8 (~CS), U6.16 ((PCINT2/OC1B/~SS~)PB2)
/SID_CSR: J13.1, JP4.3 (B), U6.18 ((PCINT4/MISO)PB4)
/SID_D0: U5.15 (D0), U6.28 ((PCINT13/SCL/ADC5)PC5), U8.15 (D0)
/SID_D1: J13.3, U5.16 (D1), U6.19 ((PCINT5/SCK)PB5), U8.16 (D1)
/SID_D2: U5.17 (D2), U6.4 ((PCINT18/INT0)PD2), U8.17 (D2)
/SID_D3: U5.18 (D3), U6.5 ((PCINT19/OC2B/INT1)PD3), U8.18 (D3)
/SID_D4: U5.19 (D4), U6.6 ((PCINT20/XCK/T0)PD4), U8.19 (D4)
/SID_D5: U5.20 (D5), U6.11 ((PCINT21/OC0B/T1)PD5), U8.20 (D5)
/SID_D6: U5.21 (D6), U6.12 ((PCINT22/OC0A/AIN0)PD6), U8.21 (D6)
/SID_D7: U5.22 (D7), U6.13 ((PCINT23/AIN1)PD7), U8.22 (D7)
/SID_L: C18.2, J8.5
/SID_R: C24.2, J8.2
/SID_RES: J13.4, U5.5 (~RESET), U6.17 ((PCINT3/OC2A/MOSI)PB3), U8.5 (~RESET)
/SID_RW: U5.7 (R/~W), U6.14 ((PCINT0/CLKO/ICP1)PB0), U8.7 (R/~W)
/XTAL1: C10.1, U6.9 (XTAL1), Y1.1
/XTAL2: C11.1, U6.10 (XTAL2), Y1.2
/~RESET: C12.2, J13.5, R17.2, SW1.2, U6.1 (~RESET)
GND: C1.2, C3.2, C4.2, C6.1, C7.2, C9.2, C10.2, C11.2, C15.2, C16.2, C21.2, C26.2, D22.1 (K), J1.2, J1.3, J2.2, J2.6, J4.2 (GND), J4.24 (GND), J5.1, J6.2 (GND), J8.1, J9.1, J12.6, J13.6, R4.1, R7.2, R8.1, R12.2, R13.2, R14.2, R15.2, R16.2, RV1.3, RV1.6, RV3.1, RV3.4, SW1.1, U1.7 (GND), U2.2 (V-), U2.4 (RLO), U2.8 (REFADJ), U3.5 (GND), U4.2 (V-), U4.4 (RLO), U4.8 (REFADJ), U5.14 (GND), U6.8 (GND), U6.22 (GND), U7.2 (-), U7.4 (GND), U8.14 (GND), U9.2 (-), U9.4 (GND)
MIDI_IN: J12.3, R20.2, U1.6, U6.2 (RXD)
MIDI_OUT: J12.2, JP3.3 (B), U6.3 (TXD)
unnamed: C12.1, J12.1
unnamed: C13.1, JP5.1 (A), R13.1, U5.27 (AUD_OUT)
unnamed: C13.2, RV3.3
unnamed: C14.1, U7.1 (GAIN)
unnamed: C14.2, U7.8 (GAIN)
unnamed: C15.1, U7.7 (BYPASS)
unnamed: C17.1, C18.1, JP5.2 (B), U7.5
unnamed: C17.2, R14.1
unnamed: C19.1, JP6.1 (A), R15.1, U8.27 (AUD_OUT)
unnamed: C19.2, RV3.6
unnamed: C20.1, U9.1 (GAIN)
unnamed: C20.2, U9.8 (GAIN)
unnamed: C21.1, U9.7 (BYPASS)
unnamed: C23.1, C24.1, JP6.2 (B), U9.5
unnamed: C23.2, R16.1
unnamed: D3.1 (K), R18.1, U3.2 (C1)
unnamed: D3.2 (A), J3.5, U3.3 (C2)
unnamed: J2.4, R2.2
unnamed: J2.5, R1.1
unnamed: J3.4, R18.2
unnamed: JP3.1 (A), R19.2, U1.1, U1.2, U3.6 (VO2)
unnamed: JP3.2 (C), U1.9, U1.10
unnamed: JP4.2 (C), U8.8 (~CS)
unnamed: Q3.2 (B), R20.1
unnamed: Q3.3 (C), R21.2
unnamed: R1.2, U1.11
unnamed: R3.1, RV1.1
unnamed: R4.2, R5.2, U2.6 (RHI)
unnamed: R6.1, RV1.4
unnamed: R7.1, U2.7 (REFOUT)
unnamed: R8.2, R9.2, U4.6 (RHI)
unnamed: R12.1, U4.7 (REFOUT)
unnamed: RV1.2, U2.5 (SIG)
unnamed: RV1.5, U4.5 (SIG)
unnamed: RV3.2, U7.3 (+)
unnamed: RV3.5, U9.3 (+)
unnamed: U1.3, U1.4, U1.5
unnamed: U1.8, U1.12, U1.13
VU_L: J5.5, J9.5, R3.2
VU_R: J5.2, J9.2, R6.2

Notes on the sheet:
DTR
RxD
TxD
VCC
GND
USB-TTL Adapter
Normally you'd want this linked across pins 1-2 to have J2 work as MIDI THRU for chaining. 2-3 makes it a MIDI OUT from the MCU, allowing the MCU to instead act as a MIDI filter module instead.
J9 serves as a simple splitter, this is handy when you don't have an audio Y-splitter cable.

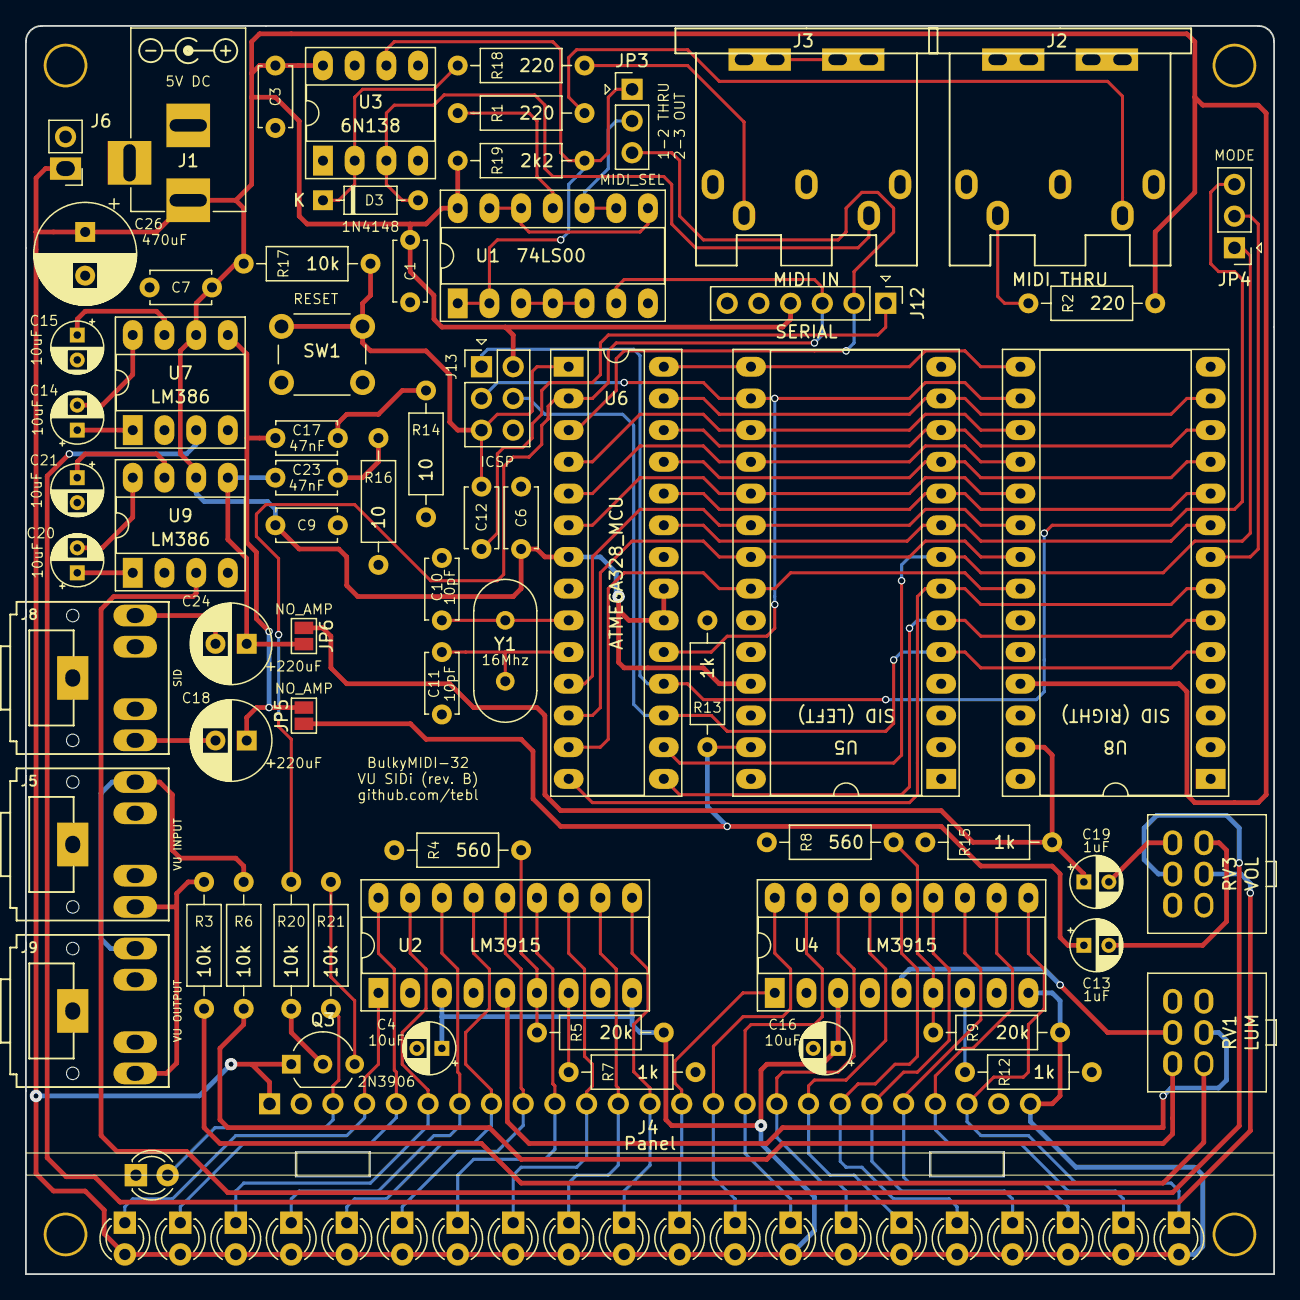
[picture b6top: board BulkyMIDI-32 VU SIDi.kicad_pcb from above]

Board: 2 copper layers, 100.0 x 100.0 mm, 95 parts (0 on the bottom side), 88 nets.
